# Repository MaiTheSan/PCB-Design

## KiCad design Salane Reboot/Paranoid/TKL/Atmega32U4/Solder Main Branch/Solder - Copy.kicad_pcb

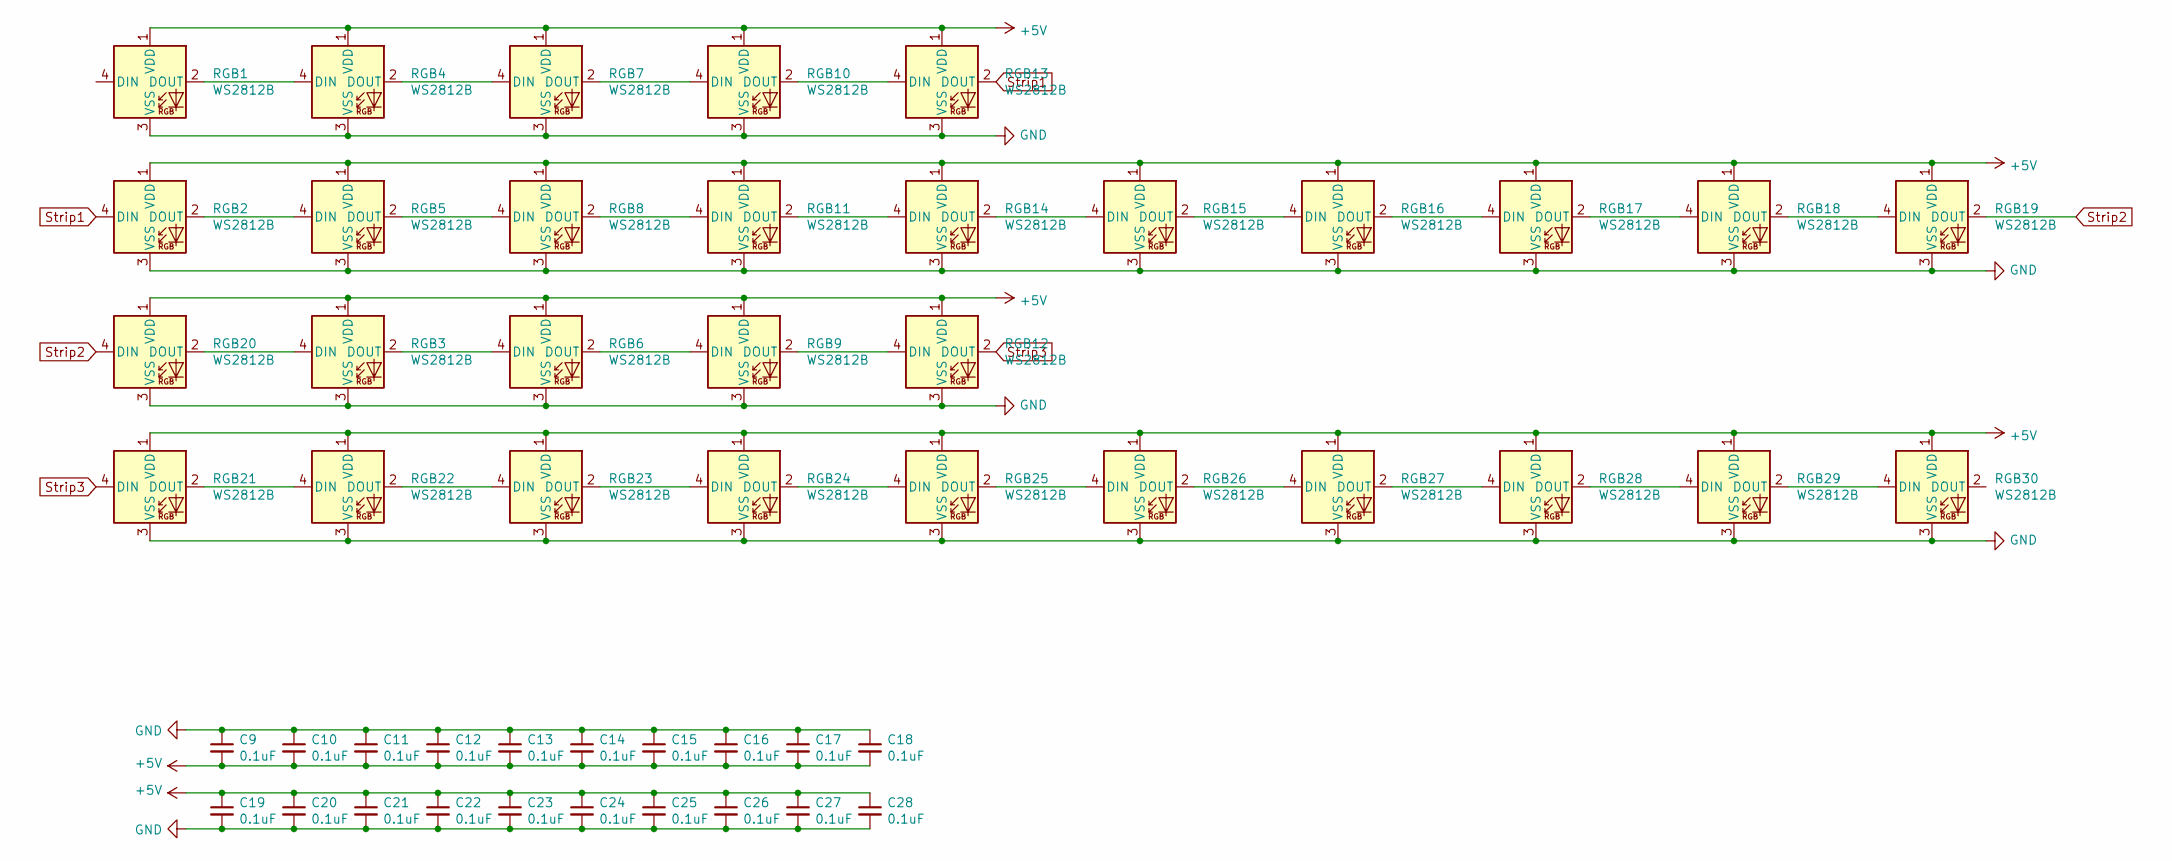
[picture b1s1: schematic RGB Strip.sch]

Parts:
C9, C10, C11, C12, C13, C14, C15, C16, C17, C18, C19, C20, C21, C22, C23, C24, C25, C26, C27, C28: 0.1uF; C_0603
RGB1, RGB2, RGB3, RGB4, RGB5, RGB6, RGB7, RGB8, RGB9, RGB10, RGB11, RGB12, RGB13, RGB14, RGB15, RGB16, RGB17, RGB18, RGB19, RGB20, RGB21, RGB22, RGB23, RGB24, RGB25, RGB26, RGB27, RGB28, RGB29, RGB30: WS2812B; LED_SK6812MINI_PLCC4_3.5x3.5mm_P1.75mm

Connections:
+5V: C9.2, C10.2, C11.2, C12.2, C13.2, C14.2, C15.2, C16.2, C17.2, C18.2, C19.1, C20.1, C21.1, C22.1, C23.1, C24.1, C25.1, C26.1, C27.1, C28.1, RGB1.1 (VDD), RGB2.1 (VDD), RGB3.1 (VDD), RGB4.1 (VDD), RGB5.1 (VDD), RGB6.1 (VDD), RGB7.1 (VDD), RGB8.1 (VDD), RGB9.1 (VDD), RGB10.1 (VDD), RGB11.1 (VDD), RGB12.1 (VDD), RGB13.1 (VDD), RGB14.1 (VDD), RGB15.1 (VDD), RGB16.1 (VDD), RGB17.1 (VDD), RGB18.1 (VDD), RGB19.1 (VDD), RGB20.1 (VDD), RGB21.1 (VDD), RGB22.1 (VDD), RGB23.1 (VDD), RGB24.1 (VDD), RGB25.1 (VDD), RGB26.1 (VDD), RGB27.1 (VDD), RGB28.1 (VDD), RGB29.1 (VDD), RGB30.1 (VDD); also elsewhere on the board
GND: C9.1, C10.1, C11.1, C12.1, C13.1, C14.1, C15.1, C16.1, C17.1, C18.1, C19.2, C20.2, C21.2, C22.2, C23.2, C24.2, C25.2, C26.2, C27.2, C28.2, RGB1.3 (VSS), RGB2.3 (VSS), RGB3.3 (VSS), RGB4.3 (VSS), RGB5.3 (VSS), RGB6.3 (VSS), RGB7.3 (VSS), RGB8.3 (VSS), RGB9.3 (VSS), RGB10.3 (VSS), RGB11.3 (VSS), RGB12.3 (VSS), RGB13.3 (VSS), RGB14.3 (VSS), RGB15.3 (VSS), RGB16.3 (VSS), RGB17.3 (VSS), RGB18.3 (VSS), RGB19.3 (VSS), RGB20.3 (VSS), RGB21.3 (VSS), RGB22.3 (VSS), RGB23.3 (VSS), RGB24.3 (VSS), RGB25.3 (VSS), RGB26.3 (VSS), RGB27.3 (VSS), RGB28.3 (VSS), RGB29.3 (VSS), RGB30.3 (VSS); also elsewhere on the board
unnamed: RGB1.2 (DOUT), RGB4.4 (DIN)
unnamed: RGB2.2 (DOUT), RGB5.4 (DIN)
unnamed: RGB3.2 (DOUT), RGB6.4 (DIN)
unnamed: RGB4.2 (DOUT), RGB7.4 (DIN)
unnamed: RGB5.2 (DOUT), RGB8.4 (DIN)
unnamed: RGB6.2 (DOUT), RGB9.4 (DIN)
unnamed: RGB10.2 (DOUT), RGB13.4 (DIN)
unnamed: RGB7.2 (DOUT), RGB10.4 (DIN)
unnamed: RGB11.2 (DOUT), RGB14.4 (DIN)
unnamed: RGB8.2 (DOUT), RGB11.4 (DIN)
unnamed: RGB9.2 (DOUT), RGB12.4 (DIN)
unnamed: RGB14.2 (DOUT), RGB15.4 (DIN)
unnamed: RGB15.2 (DOUT), RGB16.4 (DIN)
unnamed: RGB16.2 (DOUT), RGB17.4 (DIN)
unnamed: RGB17.2 (DOUT), RGB18.4 (DIN)
unnamed: RGB18.2 (DOUT), RGB19.4 (DIN)
unnamed: RGB3.4 (DIN), RGB20.2 (DOUT)
unnamed: RGB21.2 (DOUT), RGB22.4 (DIN)
unnamed: RGB22.2 (DOUT), RGB23.4 (DIN)
unnamed: RGB23.2 (DOUT), RGB24.4 (DIN)
unnamed: RGB24.2 (DOUT), RGB25.4 (DIN)
unnamed: RGB25.2 (DOUT), RGB26.4 (DIN)
unnamed: RGB26.2 (DOUT), RGB27.4 (DIN)
unnamed: RGB27.2 (DOUT), RGB28.4 (DIN)
unnamed: RGB28.2 (DOUT), RGB29.4 (DIN)
unnamed: RGB29.2 (DOUT), RGB30.4 (DIN)
Strip1: RGB2.4 (DIN), RGB13.2 (DOUT)
Strip2: RGB19.2 (DOUT), RGB20.4 (DIN)
Strip3: RGB12.2 (DOUT), RGB21.4 (DIN)

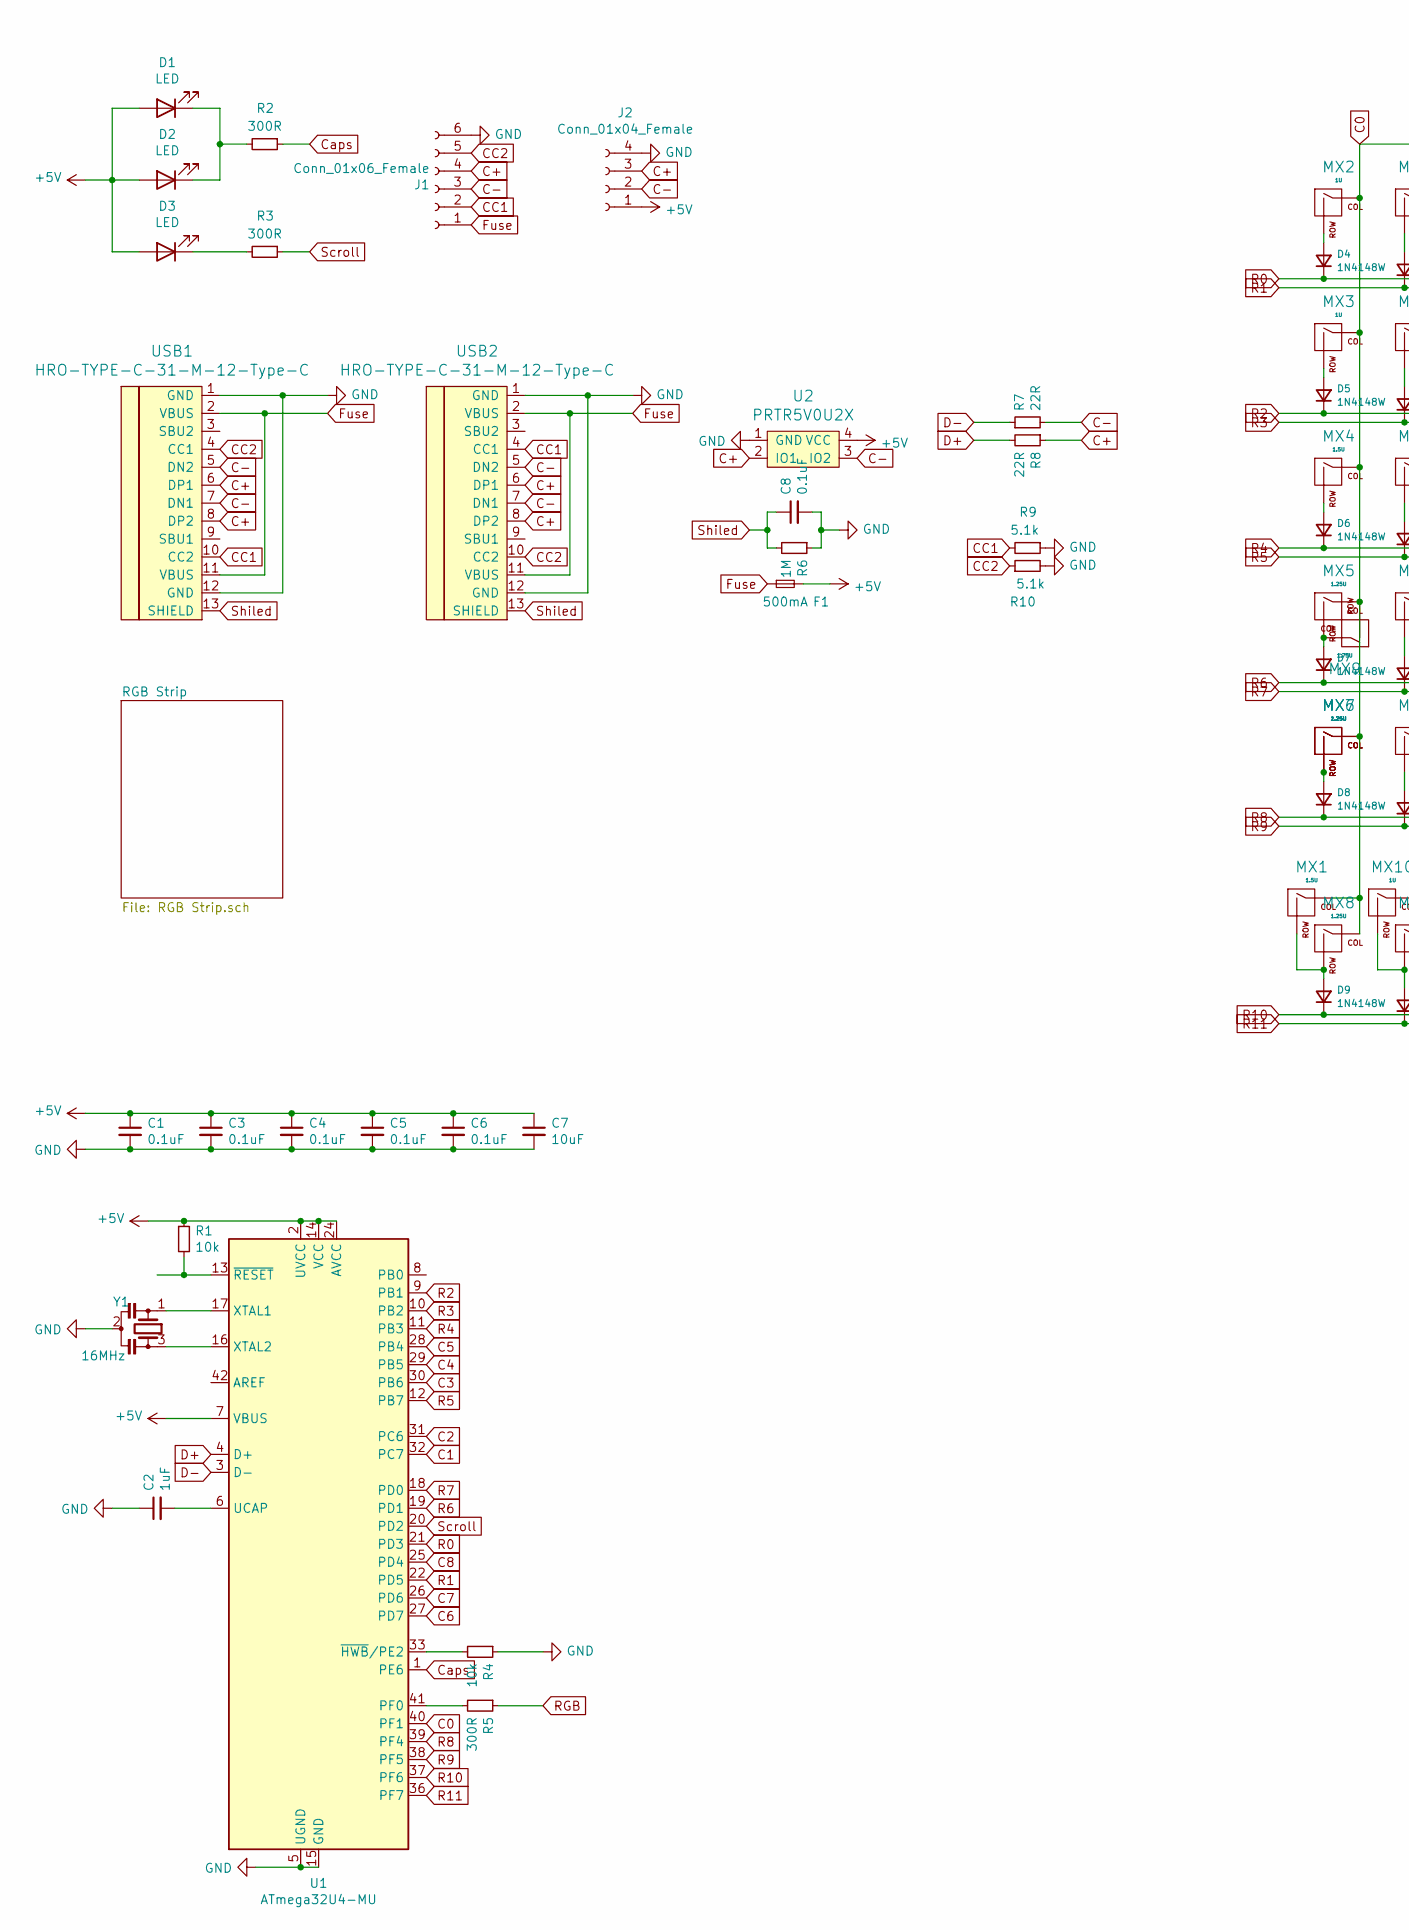
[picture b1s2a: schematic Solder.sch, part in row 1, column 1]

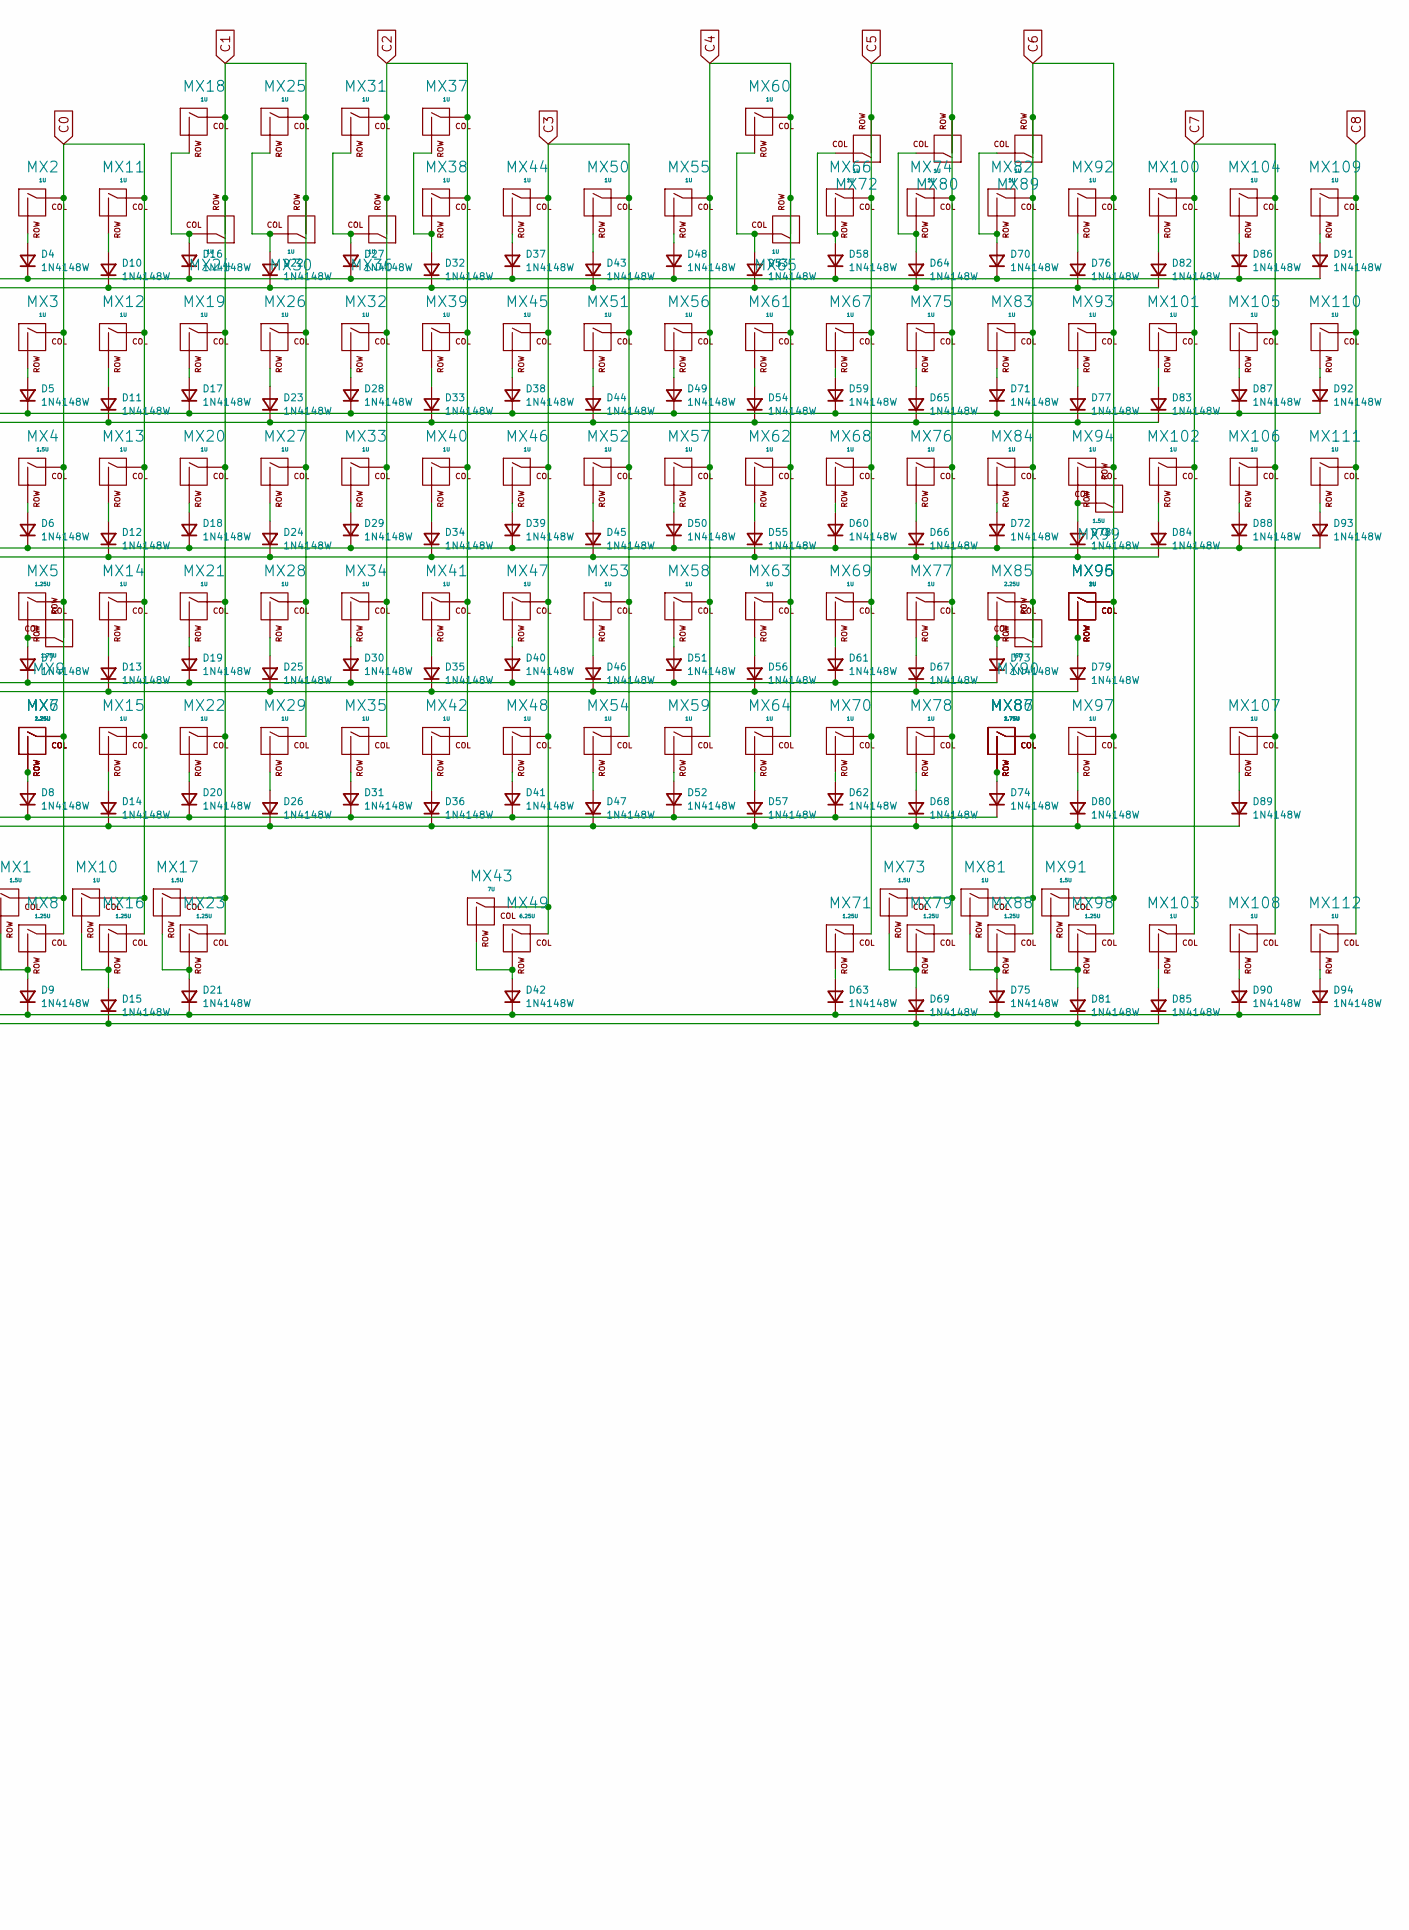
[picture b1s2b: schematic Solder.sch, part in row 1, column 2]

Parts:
C1, C3, C4, C5, C6, C8: 0.1uF; C_0402
C2: 1uF; C_0402
C7: 10uF; C_0402
D1: LED; MXOnly-LEDONLY-FLIPPED
D2, D3: LED; MXOnly-LEDONLY
D4, D5, D6, D7, D8, D9, D10, D11, D12, D13, D14, D15, D16, D17, D18, D19, D20, D21, D22, D23, D24, D25, D26, D27, D28, D29, D30, D31, D32, D33, D34, D35, D36, D37, D38, D39, D40, D41, D42, D43, D44, D45, D46, D47, D48, D49, D50, D51, D52, D53, D54, D55, D56, D57, D58, D59, D60, D61, D62, D63, D64, D65, D66, D67, D68, D69, D70, D71, D72, D73, D74, D75, D76, D77, D78, D79, D80, D81, D82, D83, D84, D85, D86, D87, D88, D89, D90, D91, D92, D93, D94: 1N4148W; DIODE_1206_SawnsProjects
F1: 500mA; Fuse_SMD1206_Reflow
J1: Conn_01x06_Female; BreakoutUSB
J2: Conn_01x04_Female; JST-SR-4
MX1, MX4, MX17, MX73, MX91, MX99: 1.5U; MXOnly-1.5U-NoLED
MX2, MX3, MX10, MX11, MX12, MX13, MX14, MX15, MX18, MX19, MX20, MX21, MX22, MX24, MX25, MX26, MX27, MX28, MX29, MX30, MX31, MX32, MX33, MX34, MX35, MX36, MX37, MX38, MX39, MX40, MX41, MX42, MX44, MX45, MX46, MX47, MX48, MX50, MX51, MX52, MX53, MX54, MX55, MX56, MX57, MX58, MX59, MX60, MX61, MX62, MX63, MX64, MX65, MX66, MX67, MX68, MX69, MX70, MX72, MX74, MX75, MX76, MX77, MX78, MX80, MX81, MX82, MX83, MX84, MX89, MX92, MX93, MX94, MX95, MX97, MX100, MX101, MX102, MX103, MX104, MX105, MX106, MX107, MX108, MX109, MX110, MX111, MX112: 1U; MXOnly-1U-NoLED
MX5, MX6, MX8, MX16, MX23, MX71, MX79, MX88, MX98: 1.25U; MXOnly-1.25U-NoLED
MX7: 2.25U; MXOnly-2.25U-NoLED
MX9, MX86: 1.75U; MXOnly-1.75U-NoLED
MX43: 7U; MXOnly-7U-ReversedStabilizers-NoLED
MX49: 6.25U; MXOnly-6.25U-ReversedStabilizers-NoLED
MX85: 2.25U; MXOnly-2.25U-ReversedStabilizers-NoLED
MX87: 2.75U; MXOnly-2.75U-NoLED
MX90: ISO; MXOnly-ISO-ROTATED-ReversedStabilizers-NoLED
MX96: 2U; MXOnly-2U-NoLED
R1, R4: 10k; R_0402
R2, R3, R5: 300R; R_0402
R6: 1M; R_0402
R7, R8: 22R; R_0402
R9, R10: 5.1k; R_0402
U1: ATmega32U4-MU; QFN-44-1EP_7x7mm_P0.5mm_EP5.2x5.2mm
U2: PRTR5V0U2X; SOT143B
USB1, USB2: HRO-TYPE-C-31-M-12-Type-C; HRO-TYPE-C-31-M-12-Assembly
Y1: 16MHz; Resonator_SMD_muRata_CSTxExxV-3Pin_3.0x1.1mm

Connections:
+5V: C1.1, C3.1, C4.1, C5.1, C6.1, C7.1, D1.2 (A), D2.2 (A), D3.2 (A), F1.2, J2.1, R1.1, U1.2 (UVCC), U1.7 (VBUS), U1.14 (VCC), U1.24 (AVCC), U1.34 (VCC), U1.44 (AVCC), U2.4 (VCC); also elsewhere on the board
C0: MX1.1 (COL), MX2.1 (COL), MX3.1 (COL), MX4.1 (COL), MX5.1 (COL), MX6.1 (COL), MX7.1 (COL), MX8.1 (COL), MX9.2 (ROW), MX10.1 (COL), MX11.1 (COL), MX12.1 (COL), MX13.1 (COL), MX14.1 (COL), MX15.1 (COL), MX16.1 (COL), U1.40 (PF1)
C1: MX17.1 (COL), MX18.1 (COL), MX19.1 (COL), MX20.1 (COL), MX21.1 (COL), MX22.1 (COL), MX23.1 (COL), MX24.2 (ROW), MX25.1 (COL), MX26.1 (COL), MX27.1 (COL), MX28.1 (COL), MX29.1 (COL), MX30.2 (ROW), U1.32 (PC7)
C2: MX31.1 (COL), MX32.1 (COL), MX33.1 (COL), MX34.1 (COL), MX35.1 (COL), MX36.2 (ROW), MX37.1 (COL), MX38.1 (COL), MX39.1 (COL), MX40.1 (COL), MX41.1 (COL), MX42.1 (COL), U1.31 (PC6)
C3: MX43.1 (COL), MX44.1 (COL), MX45.1 (COL), MX46.1 (COL), MX47.1 (COL), MX48.1 (COL), MX49.1 (COL), MX50.1 (COL), MX51.1 (COL), MX52.1 (COL), MX53.1 (COL), MX54.1 (COL), U1.30 (PB6)
C4: MX55.1 (COL), MX56.1 (COL), MX57.1 (COL), MX58.1 (COL), MX59.1 (COL), MX60.1 (COL), MX61.1 (COL), MX62.1 (COL), MX63.1 (COL), MX64.1 (COL), MX65.2 (ROW), U1.29 (PB5)
C5: MX66.1 (COL), MX67.1 (COL), MX68.1 (COL), MX69.1 (COL), MX70.1 (COL), MX71.1 (COL), MX72.2 (ROW), MX73.1 (COL), MX74.1 (COL), MX75.1 (COL), MX76.1 (COL), MX77.1 (COL), MX78.1 (COL), MX79.1 (COL), MX80.2 (ROW), U1.28 (PB4)
C6: MX81.1 (COL), MX82.1 (COL), MX83.1 (COL), MX84.1 (COL), MX85.1 (COL), MX86.1 (COL), MX87.1 (COL), MX88.1 (COL), MX89.2 (ROW), MX90.2 (ROW), MX91.1 (COL), MX92.1 (COL), MX93.1 (COL), MX94.1 (COL), MX95.1 (COL), MX96.1 (COL), MX97.1 (COL), MX98.1 (COL), MX99.2 (ROW), U1.27 (PD7)
C7: MX100.1 (COL), MX101.1 (COL), MX102.1 (COL), MX103.1 (COL), MX104.1 (COL), MX105.1 (COL), MX106.1 (COL), MX107.1 (COL), MX108.1 (COL), U1.26 (PD6)
C8: MX109.1 (COL), MX110.1 (COL), MX111.1 (COL), MX112.1 (COL), U1.25 (PD4)
C+: J1.4, J2.3, R8.1, U2.2 (IO1), USB1.6 (DP1), USB1.8 (DP2), USB2.6 (DP1), USB2.8 (DP2)
C-: J1.3, J2.2, R7.2, U2.3 (IO2), USB1.5 (DN2), USB1.7 (DN1), USB2.5 (DN2), USB2.7 (DN1)
CC1: J1.2, R9.2, USB1.10 (CC2), USB2.4 (CC1)
CC2: J1.5, R10.1, USB1.4 (CC1), USB2.10 (CC2)
Caps: R2.1, U1.1 (PE6)
D+: R8.2, U1.4 (D+)
D-: R7.1, U1.3 (D-)
Fuse: F1.1, J1.1, USB1.2 (VBUS), USB1.11 (VBUS), USB2.2 (VBUS), USB2.11 (VBUS)
GND: C1.2, C2.1, C3.2, C4.2, C5.2, C6.2, C7.2, C8.2, J1.6, J2.4, R4.1, R6.1, R9.1, R10.2, U1.5 (UGND), U1.15 (GND), U1.23 (GND), U1.35 (GND), U1.43 (GND), U1.45 (GND), U2.1 (GND), USB1.1 (GND), USB1.12 (GND), USB2.1 (GND), USB2.12 (GND), Y1.2; also elsewhere on the board
unnamed: C2.2, U1.6 (UCAP)
unnamed: D1.1 (K), D2.1 (K), R2.2
unnamed: D3.1 (K), R3.2
unnamed: D4.2 (A), MX2.2 (ROW)
unnamed: D5.2 (A), MX3.2 (ROW)
unnamed: D6.2 (A), MX4.2 (ROW)
unnamed: D7.2 (A), MX5.2 (ROW), MX9.1 (COL)
unnamed: D8.2 (A), MX6.2 (ROW), MX7.2 (ROW)
unnamed: D9.2 (A), MX1.2 (ROW), MX8.2 (ROW)
unnamed: D10.2 (A), MX11.2 (ROW)
unnamed: D11.2 (A), MX12.2 (ROW)
unnamed: D12.2 (A), MX13.2 (ROW)
unnamed: D13.2 (A), MX14.2 (ROW)
unnamed: D14.2 (A), MX15.2 (ROW)
unnamed: D15.2 (A), MX10.2 (ROW), MX16.2 (ROW)
unnamed: D16.2 (A), MX18.2 (ROW), MX24.1 (COL)
unnamed: D17.2 (A), MX19.2 (ROW)
unnamed: D18.2 (A), MX20.2 (ROW)
unnamed: D19.2 (A), MX21.2 (ROW)
unnamed: D20.2 (A), MX22.2 (ROW)
unnamed: D21.2 (A), MX17.2 (ROW), MX23.2 (ROW)
unnamed: D22.2 (A), MX25.2 (ROW), MX30.1 (COL)
unnamed: D23.2 (A), MX26.2 (ROW)
unnamed: D24.2 (A), MX27.2 (ROW)
unnamed: D25.2 (A), MX28.2 (ROW)
unnamed: D26.2 (A), MX29.2 (ROW)
unnamed: D27.2 (A), MX31.2 (ROW), MX36.1 (COL)
unnamed: D28.2 (A), MX32.2 (ROW)
unnamed: D29.2 (A), MX33.2 (ROW)
unnamed: D30.2 (A), MX34.2 (ROW)
unnamed: D31.2 (A), MX35.2 (ROW)
unnamed: D32.2 (A), MX37.2 (ROW), MX38.2 (ROW)
unnamed: D33.2 (A), MX39.2 (ROW)
unnamed: D34.2 (A), MX40.2 (ROW)
unnamed: D35.2 (A), MX41.2 (ROW)
unnamed: D36.2 (A), MX42.2 (ROW)
unnamed: D37.2 (A), MX44.2 (ROW)
unnamed: D38.2 (A), MX45.2 (ROW)
unnamed: D39.2 (A), MX46.2 (ROW)
unnamed: D40.2 (A), MX47.2 (ROW)
unnamed: D41.2 (A), MX48.2 (ROW)
unnamed: D42.2 (A), MX43.2 (ROW), MX49.2 (ROW)
unnamed: D43.2 (A), MX50.2 (ROW)
unnamed: D44.2 (A), MX51.2 (ROW)
unnamed: D45.2 (A), MX52.2 (ROW)
unnamed: D46.2 (A), MX53.2 (ROW)
unnamed: D47.2 (A), MX54.2 (ROW)
unnamed: D48.2 (A), MX55.2 (ROW)
unnamed: D49.2 (A), MX56.2 (ROW)
unnamed: D50.2 (A), MX57.2 (ROW)
unnamed: D51.2 (A), MX58.2 (ROW)
unnamed: D52.2 (A), MX59.2 (ROW)
unnamed: D53.2 (A), MX60.2 (ROW), MX65.1 (COL)
unnamed: D54.2 (A), MX61.2 (ROW)
unnamed: D55.2 (A), MX62.2 (ROW)
unnamed: D56.2 (A), MX63.2 (ROW)
unnamed: D57.2 (A), MX64.2 (ROW)
unnamed: D58.2 (A), MX66.2 (ROW), MX72.1 (COL)
unnamed: D59.2 (A), MX67.2 (ROW)
unnamed: D60.2 (A), MX68.2 (ROW)
unnamed: D61.2 (A), MX69.2 (ROW)
unnamed: D62.2 (A), MX70.2 (ROW)
unnamed: D63.2 (A), MX71.2 (ROW)
unnamed: D64.2 (A), MX74.2 (ROW), MX80.1 (COL)
unnamed: D65.2 (A), MX75.2 (ROW)
unnamed: D66.2 (A), MX76.2 (ROW)
unnamed: D67.2 (A), MX77.2 (ROW)
unnamed: D68.2 (A), MX78.2 (ROW)
unnamed: D69.2 (A), MX73.2 (ROW), MX79.2 (ROW)
unnamed: D70.2 (A), MX82.2 (ROW), MX89.1 (COL)
unnamed: D71.2 (A), MX83.2 (ROW)
unnamed: D72.2 (A), MX84.2 (ROW)
unnamed: D73.2 (A), MX85.2 (ROW), MX90.1 (COL)
unnamed: D74.2 (A), MX86.2 (ROW), MX87.2 (ROW)
unnamed: D75.2 (A), MX81.2 (ROW), MX88.2 (ROW)
unnamed: D76.2 (A), MX92.2 (ROW)
unnamed: D77.2 (A), MX93.2 (ROW)
unnamed: D78.2 (A), MX94.2 (ROW), MX99.1 (COL)
unnamed: D79.2 (A), MX95.2 (ROW), MX96.2 (ROW)
unnamed: D80.2 (A), MX97.2 (ROW)
unnamed: D81.2 (A), MX91.2 (ROW), MX98.2 (ROW)
unnamed: D82.2 (A), MX100.2 (ROW)
unnamed: D83.2 (A), MX101.2 (ROW)
unnamed: D84.2 (A), MX102.2 (ROW)
unnamed: D85.2 (A), MX103.2 (ROW)
unnamed: D86.2 (A), MX104.2 (ROW)
unnamed: D87.2 (A), MX105.2 (ROW)
unnamed: D88.2 (A), MX106.2 (ROW)
unnamed: D89.2 (A), MX107.2 (ROW)
unnamed: D90.2 (A), MX108.2 (ROW)
unnamed: D91.2 (A), MX109.2 (ROW)
unnamed: D92.2 (A), MX110.2 (ROW)
unnamed: D93.2 (A), MX111.2 (ROW)
unnamed: D94.2 (A), MX112.2 (ROW)
unnamed: R1.2, U1.13 (~RESET)
unnamed: R4.2, U1.33 (~HWB~/PE2)
unnamed: R5.2, U1.41 (PF0)
unnamed: U1.16 (XTAL2), Y1.3
unnamed: U1.17 (XTAL1), Y1.1
R0: D4.1 (K), D16.1 (K), D27.1 (K), D37.1 (K), D48.1 (K), D58.1 (K), D70.1 (K), D86.1 (K), D91.1 (K), U1.21 (PD3)
R1: D10.1 (K), D22.1 (K), D32.1 (K), D43.1 (K), D53.1 (K), D64.1 (K), D76.1 (K), D82.1 (K), U1.22 (PD5)
R2: D5.1 (K), D17.1 (K), D28.1 (K), D38.1 (K), D49.1 (K), D59.1 (K), D71.1 (K), D87.1 (K), D92.1 (K), U1.9 (PB1)
R3: D11.1 (K), D23.1 (K), D33.1 (K), D44.1 (K), D54.1 (K), D65.1 (K), D77.1 (K), D83.1 (K), U1.10 (PB2)
R4: D6.1 (K), D18.1 (K), D29.1 (K), D39.1 (K), D50.1 (K), D60.1 (K), D72.1 (K), D88.1 (K), D93.1 (K), U1.11 (PB3)
R5: D12.1 (K), D24.1 (K), D34.1 (K), D45.1 (K), D55.1 (K), D66.1 (K), D78.1 (K), D84.1 (K), U1.12 (PB7)
R6: D7.1 (K), D19.1 (K), D30.1 (K), D40.1 (K), D51.1 (K), D61.1 (K), D73.1 (K), U1.19 (PD1)
R7: D13.1 (K), D25.1 (K), D35.1 (K), D46.1 (K), D56.1 (K), D67.1 (K), D79.1 (K), U1.18 (PD0)
R8: D8.1 (K), D20.1 (K), D31.1 (K), D41.1 (K), D52.1 (K), D62.1 (K), D74.1 (K), U1.39 (PF4)
R9: D14.1 (K), D26.1 (K), D36.1 (K), D47.1 (K), D57.1 (K), D68.1 (K), D80.1 (K), D89.1 (K), U1.38 (PF5)
R10: D9.1 (K), D21.1 (K), D42.1 (K), D63.1 (K), D75.1 (K), D90.1 (K), D94.1 (K), U1.37 (PF6)
R11: D15.1 (K), D69.1 (K), D81.1 (K), D85.1 (K), U1.36 (PF7)
Scroll: R3.1, U1.20 (PD2)
Shiled: C8.1, R6.2, USB1.13 (SHIELD), USB2.13 (SHIELD)

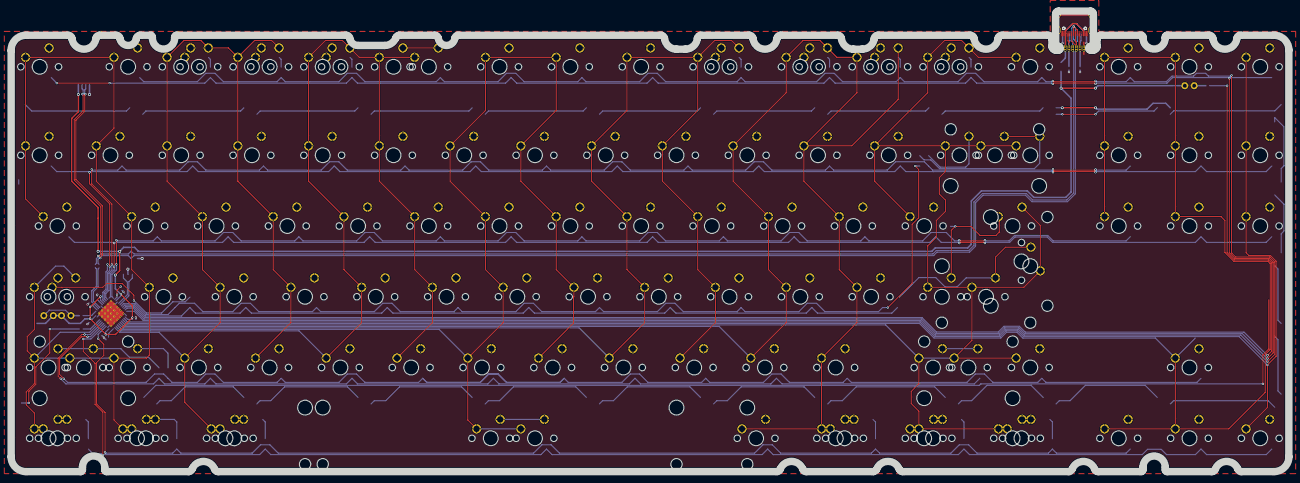
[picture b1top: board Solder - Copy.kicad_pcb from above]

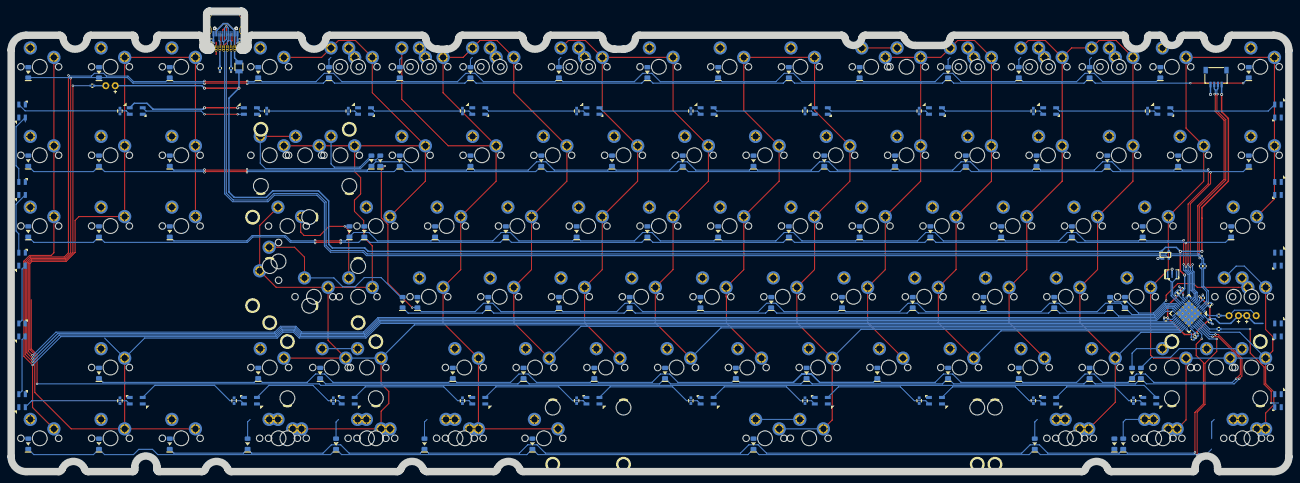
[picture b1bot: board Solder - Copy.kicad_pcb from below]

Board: 2 copper layers, 344.0 x 124.0 mm, 282 parts (165 on the bottom side), 161 nets.
